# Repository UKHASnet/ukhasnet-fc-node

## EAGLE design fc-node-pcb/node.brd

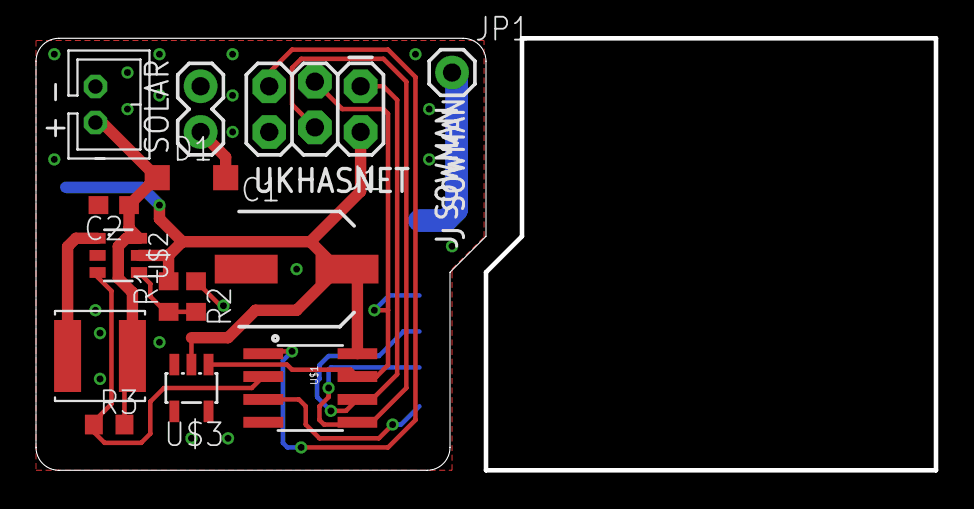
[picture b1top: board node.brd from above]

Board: 2 copper layers, 50.0 x 24.0 mm, 15 parts (1 on the bottom side), 13 nets.

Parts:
C1: 100u; SANYO-OSCON_SMD_C6
C2: 4u7; C0603
D1: SOD123
DF: 4u7; BOURNS_SRN5040_L
J1: AVR_SPI_PRG_62X3_LOCK; 2X3_LOCK
J2: JST-2-TH
JP1: M01PTH; 1X01
R1, R2, R3: R0603
SOLAR: M02PTH; 1X02
U$1: ATTINY13SOIC; SO08
U$2: MCP1640; SOT23-6
U$3: BU49X_VDET_SOT235; SOT23-5L
U$4: RFM69HW; RFM

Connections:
DET/SCK: J1.3, U$1.7, U$3.1, U$4.SCK
GND: C1.-, C2.2, J1.6, J2.2, R2.1, SOLAR.2, U$1.4, U$2.2, U$3.3, U$4.GNDA, U$4.GNDB
MISO: J1.1, U$1.6, U$4.MISO
MOSI: J1.4, U$1.5, U$4.MOSI
unnamed: DF.P$2, U$2.1
unnamed: R1.1, R2.2, U$2.4
unnamed: JP1.1, U$4.ANT
unnamed: R3.1, U$1.2, U$2.3
unnamed: D1.A, SOLAR.1
RESET: J1.5, U$1.1
RFM_SS: U$1.3, U$4.NSS
VBATT: C2.1, D1.C, DF.P$1, J2.1, R3.2, U$2.6
VCC: C1.+, J1.2, R1.2, U$1.8, U$2.5, U$3.2, U$4.VCC

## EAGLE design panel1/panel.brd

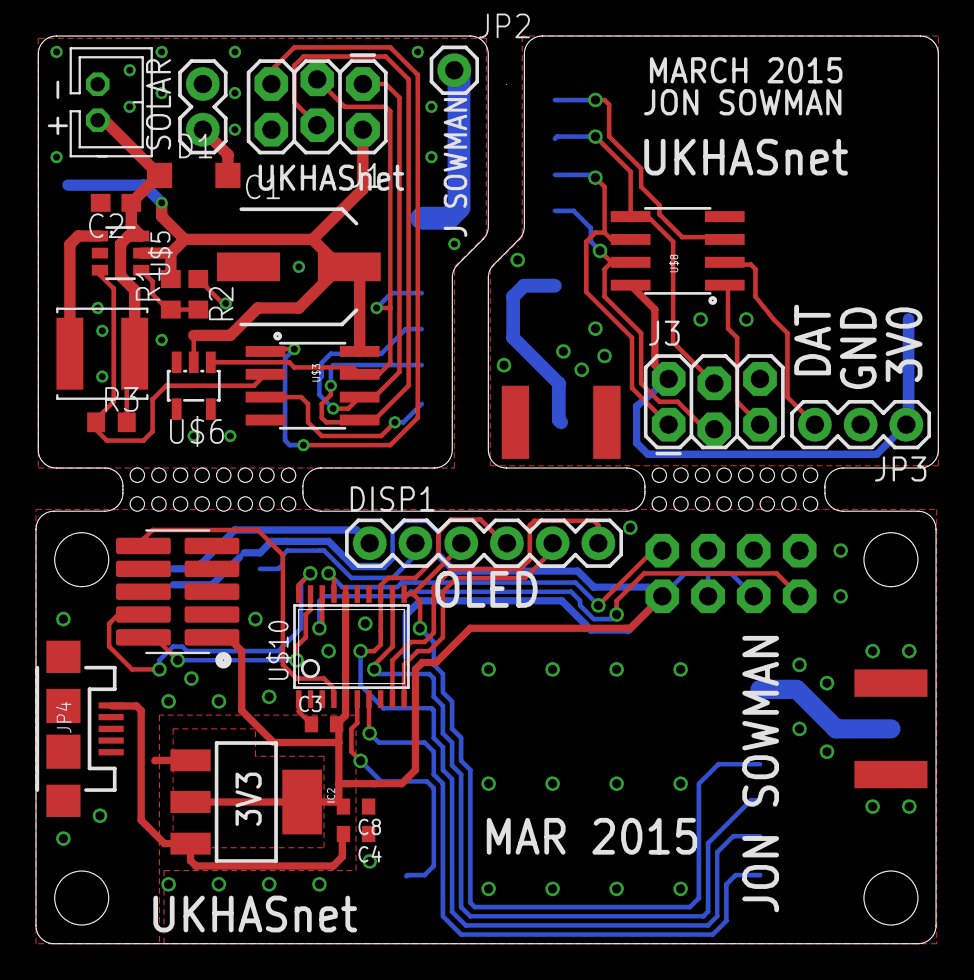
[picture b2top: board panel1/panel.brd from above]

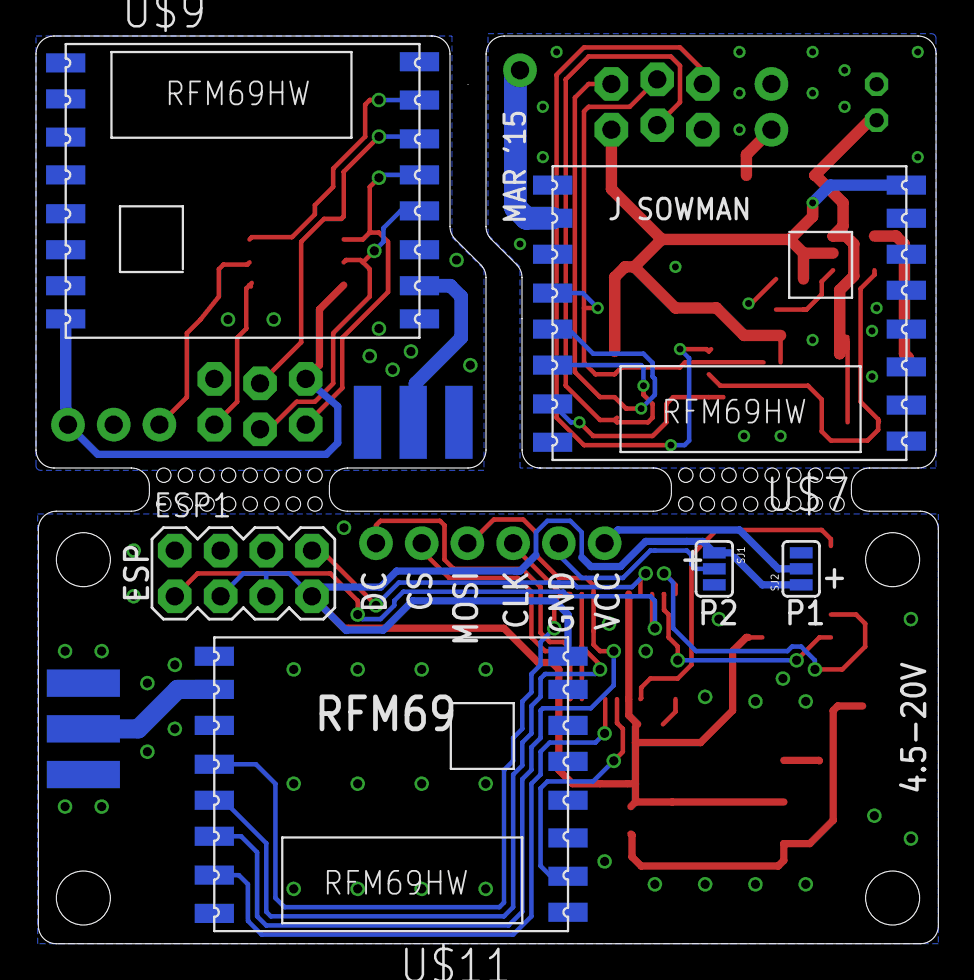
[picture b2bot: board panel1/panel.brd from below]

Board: 2 copper layers, 50.1 x 50.4 mm, 33 parts (8 on the bottom side), 40 nets.

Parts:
C1: 100u; SANYO-OSCON_SMD_C6
C2: 4u7; C0603
C3, C4, C8: 100n; C0603-L
D1: SOD123
DF: 4u7; BOURNS_SRN5040_L
DISP1: 1X06
ESP1: M04X2; 2X4
IC2: SOT223
J1, J3: AVR_SPI_PRG_62X3_LOCK; 2X3_LOCK
J2: JST-2-TH
J$2, J$3: SMA_EDGE; SMA-EDGE
JP2: M01PTH; 1X01
JP3: 1X03
JP4: USB-MICROB
R1, R2, R3: R0603
SJ1, SJ2: SJ_3
SOLAR: M02PTH; 1X02
U$3, U$8: ATTINY13SOIC; SO08
U$5: MCP1640; SOT23-6
U$6: BU49X_VDET_SOT235; SOT23-5L
U$7, U$9, U$11: RFM69HW; RFM
U$10: STM32F030F4; TSSOP20
U$12: SWD_SHROUD_SMD; SWD_SMD_SHROUD

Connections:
DATA: JP3.3, U$8.2
DET/SCK: J1.3, U$3.7, U$6.1, U$7.SCK
DISPLAY_CS1: DISP1.5, U$10.10
DISPLAY_DC1: DISP1.6, U$10.9
GND1: C1.-, C2.2, J1.6, J2.2, R2.1, SOLAR.2, U$3.4, U$5.2, U$6.3, U$7.GNDA, U$7.GNDB
GND2: J3.6, J$2.GND@0, J$2.GND@1, J$2.GND@2, J$2.GND@3, JP3.2, U$8.4, U$9.GNDA, U$9.GNDB
GND3: C3.1, C4.1, C8.1, ESP1.2, IC2.1, J$3.GND@0, J$3.GND@1, J$3.GND@2, J$3.GND@3, JP4.GND, JP4.MT1, JP4.MT2, SJ1.3, SJ2.3, U$10.1, U$10.15, U$11.GNDA, U$11.GNDB, U$12.3, U$12.5, U$12.7, U$12.9
MISO1: J1.1, U$3.6, U$7.MISO
MISO2: J3.1, U$8.6, U$9.MISO
MISO3: U$10.12, U$11.MISO
MOSI1: J1.4, U$3.5, U$7.MOSI
MOSI2: J3.4, U$8.5, U$9.MOSI
MOSI3: DISP1.4, U$10.13, U$11.MOSI
unnamed: DF.P$2, U$5.1
unnamed: R3.1, U$3.2, U$5.3
unnamed: R1.1, R2.2, U$5.4
unnamed: JP2.1, U$7.ANT
unnamed: D1.A, SOLAR.1
unnamed: J$2.SIG, U$9.ANT
unnamed: J$3.SIG, U$11.ANT
unnamed: C4.2, IC2.3, JP4.VBUS
unnamed: U$10.6, U$11.DIO0
unnamed: DISP1.2, SJ1.2
unnamed: DISP1.1, SJ2.2
NRST1: U$10.4, U$12.10
RESET: J1.5, U$3.1
RESET1: J3.5, U$8.1
RFM_CS1: U$10.7, U$11.NSS
RFM_SS: U$3.3, U$7.NSS
RFM_SS1: U$8.3, U$9.NSS
SCK1: J3.3, U$8.7, U$9.SCK
SCK2: DISP1.3, U$10.11, U$11.SCK
SWCLK1: U$10.20, U$12.4
SWDAT1: U$10.19, U$12.2
UART_RX1: ESP1.1, U$10.18
UART_TX1: ESP1.8, U$10.17
VBATT: C2.1, D1.C, DF.P$1, J2.1, R3.2, U$5.6
VCC1: C1.+, J1.2, R1.2, U$3.8, U$5.5, U$6.2, U$7.VCC
VCC2: J3.2, JP3.1, U$8.8, U$9.VCC
VCC3: C3.2, C8.2, ESP1.3, ESP1.7, IC2.2, IC2.4, SJ1.1, SJ2.1, U$10.5, U$10.16, U$11.VCC, U$12.1

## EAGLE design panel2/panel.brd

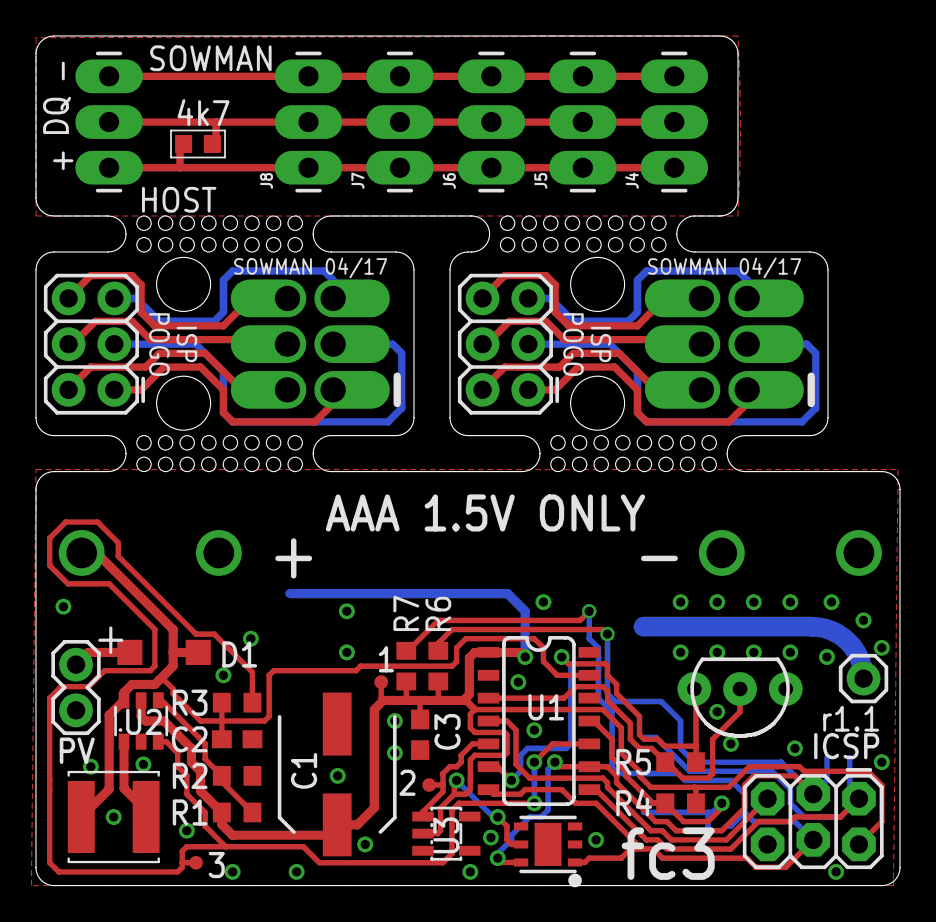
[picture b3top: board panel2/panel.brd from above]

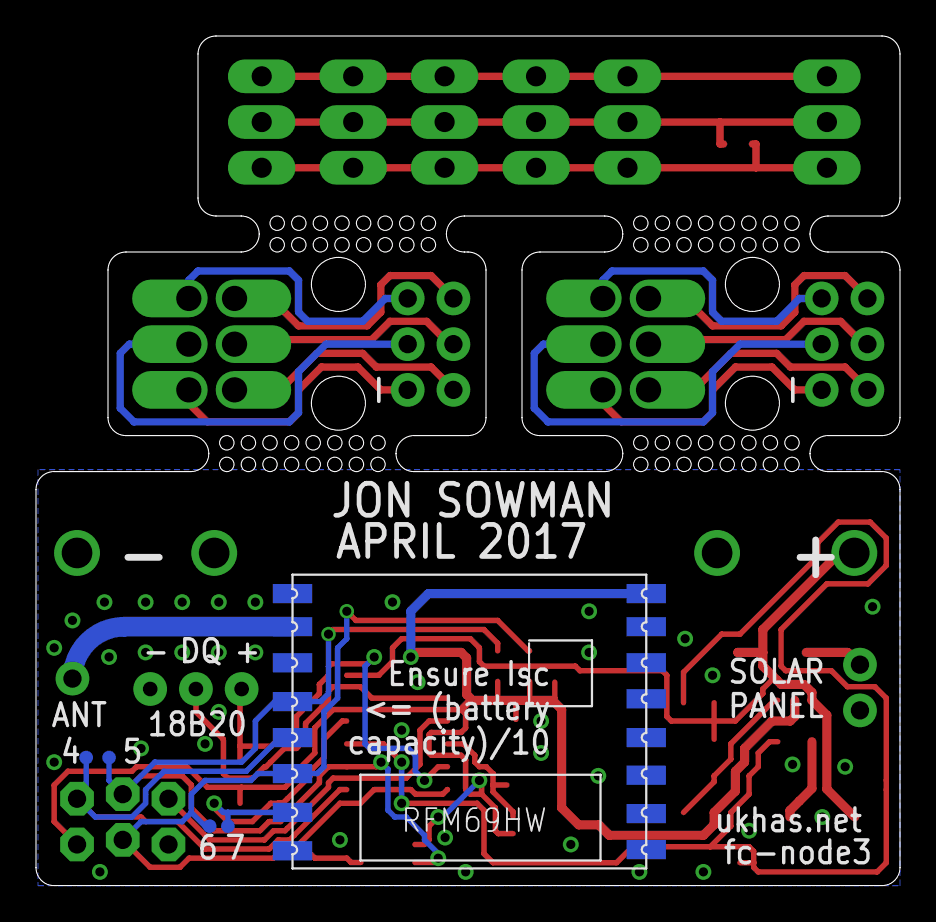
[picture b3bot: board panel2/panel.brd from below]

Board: 2 copper layers, 48.0 x 47.2 mm, 40 parts (5 on the bottom side), 31 nets.

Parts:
BAT1: BATTERY-AAA
C1: 100u; SANYO-OSCON_SMD_C6
C2: 4u7; C0603
C3: 100n; C0603
D1: SOD123
DF: 4u7; BOURNS_SRN5040_L
HOST: 1X03_LONGPADS
IC1: HTU21D; DFN6-L
J1: AVR_SPI_PRG_62X3_LOCK; 2X3_LOCK
J2, J3: AVR_SPI_PROG_3X2PTH; 2X3
J4, J5, J6, J7, J8: 1X03_LONGPADS
JP1: M01PTH; 1X01
R1, R2, R3, R4, R5, R6, R7: R0603
R8: R0603-N
SOLAR: M02PTH; 1X02
TP1, TP2, TP3, TP4, TP5, TP6, TP7: TEST-POINT3; PAD.03X.03
U1: ATTINY84; SO14
U2: MCP1640; SOT23-6
U3: BU49X_VDET_SOT235; SOT23-5L
U5: DS18B20; TO-92-AMMO
U$1, U$2: AVR_SPI_PROG_3X2_POGO; 2X3-POGO
U$4: RFM69HW; RFM

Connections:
1: HOST.1, J4.1, J5.1, J6.1, J7.1, J8.1, R8.1
2: HOST.2, J4.2, J5.2, J6.2, J7.2, J8.2, R8.2
3: HOST.3, J4.3, J5.3, J6.3, J7.3, J8.3
18B20_DQ: R5.1, U1.3, U5.2
18B20_VDD: R5.2, U1.6, U5.3
DET: TP2.P$1, U1.5, U3.1
EN: R3.1, TP3.P$1, U1.10, U2.3
GND: BAT1.GND@1, C1.-, C2.2, C3.2, IC1.2, J1.6, R2.1, SOLAR.2, U1.14, U2.2, U3.3, U5.1, U$4.GNDA, U$4.GNDB
MISO: J1.1, TP6.P$1, U1.8, U$4.MISO
MOSI: IC1.1, J1.4, R7.1, TP5.P$1, U1.7, U$4.MOSI
unnamed: DF.P$2, U2.1
unnamed: R1.1, R2.2, U2.4
unnamed: JP1.1, U$4.ANT
unnamed: J2.1, U$1.1
unnamed: D1.A, SOLAR.1
unnamed: J2.3, U$1.3
unnamed: J2.5, U$1.5
unnamed: J2.2, U$1.2
unnamed: J2.4, U$1.4
unnamed: J2.6, U$1.6
unnamed: J3.1, U$2.1
unnamed: J3.3, U$2.3
unnamed: J3.5, U$2.5
unnamed: J3.2, U$2.2
unnamed: J3.4, U$2.4
unnamed: J3.6, U$2.6
RESET: J1.5, U1.4
RFM_SS: R4.1, TP4.P$1, U1.11, U$4.NSS
SCK: IC1.6, J1.3, R6.1, TP7.P$1, U1.9, U$4.SCK
VBATT: BAT1.PWR@1, C2.1, D1.C, DF.P$1, R3.2, U1.13, U2.6
VCC: C1.+, C3.1, IC1.5, J1.2, R1.2, R4.2, R6.2, R7.2, TP1.P$1, U1.1, U2.5, U3.2, U$4.VCC

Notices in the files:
parts and their libraries:
SparkFun-DigitalIC: Licensing: Creative Commons ShareAlike 4.0 International - https://creativecommons.org/licenses/by-sa/4.0
